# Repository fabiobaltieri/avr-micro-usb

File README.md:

AVR MICRO USB
==========

This project is a small USB key based on Atmel ATtiny45-like microcontrollers.

License
-------

This program is free software: you can redistribute it and/or modify
it under the terms of the GNU General Public License as published by
the Free Software Foundation, either version 2 of the License, or
(at your option) any later version.

Contents
--------

    COPYING     text version of the GPL
    README      this file
    firmware/   source directory for firmware files
    hardware/   source directory for the hardware design files

Firmware
--------

Building requires an avr-gcc toolchain, in the firmware/ directory, to build
run:

    make main.hex

Flashing the firmware on the device requires avrdude and a compatible hardware
programmer. Default configuration is stored at the beginning of the Makefile.
To program with the default configuration, run:

    make flash

Fuses can be configured running:

    make fuses

Hardware
--------

All hardware files (schematic, layout and libraries) are in CadSoft Eagle
format.

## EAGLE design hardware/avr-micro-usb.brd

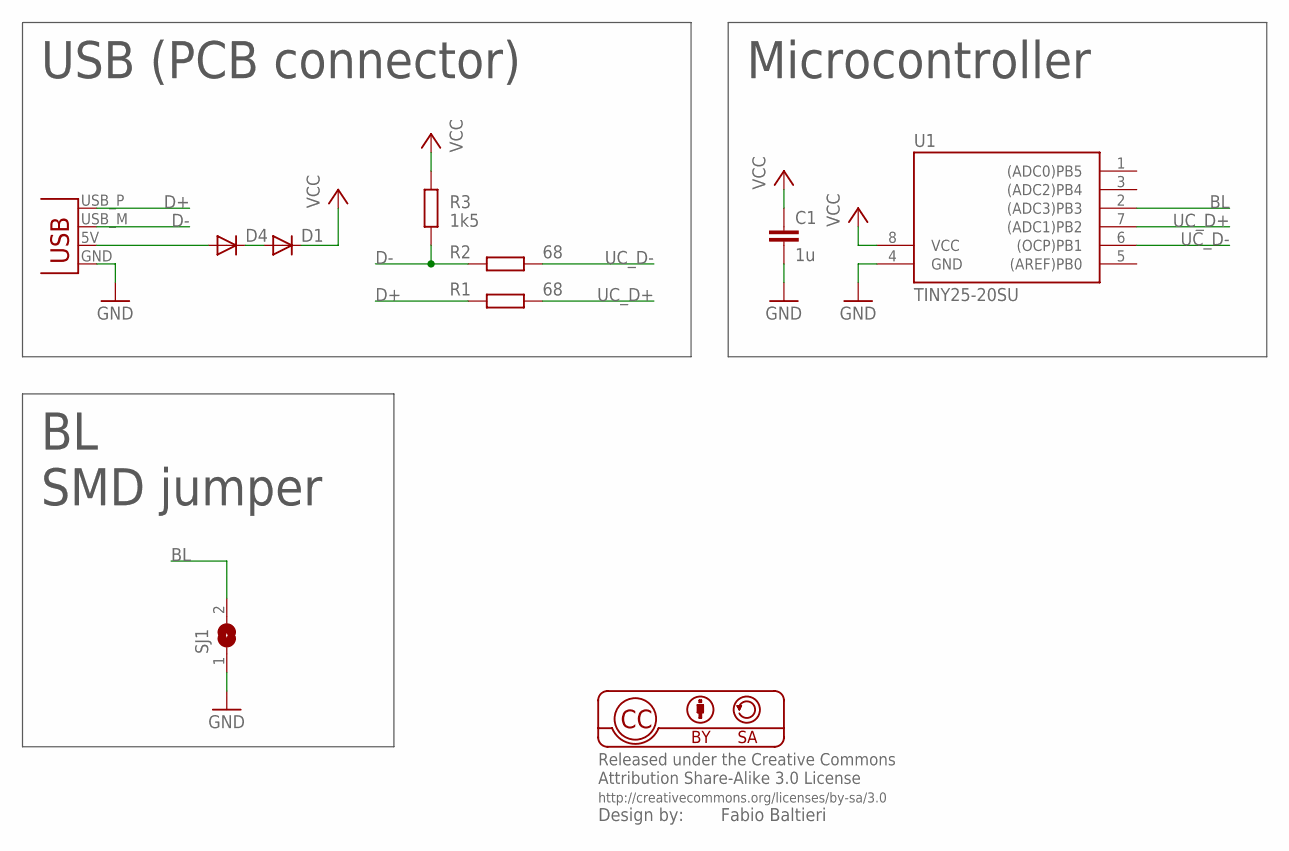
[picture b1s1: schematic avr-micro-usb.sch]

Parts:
C1: 1u; C0805
D1, D4: DIODE-MINIMELF; MINIMELF
R1, R2: 68; R0603
R3: 1k5; R0603
SJ1: SJ
U1: TINY25-20SU; SOIC8
X1: USBPCB; USB-A-PCB

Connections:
BL: SJ1.2, U1.2 ((ADC3)PB3)
D+: R1.2, X1.USB_P (D+)
D-: R2.2, R3.1, X1.USB_M (D-)
GND: C1.2, SJ1.1, U1.4 (GND), X1.GND
unnamed: D4.A, X1.5V (VBUS)
unnamed: D1.A, D4.C
UC_D+: R1.1, U1.7 ((ADC1)PB2)
UC_D-: R2.1, U1.6 ((OCP)PB1)
VCC: C1.1, D1.C, R3.2, U1.8 (VCC)

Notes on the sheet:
USB (PCB connector)
SMD jumper
Microcontroller

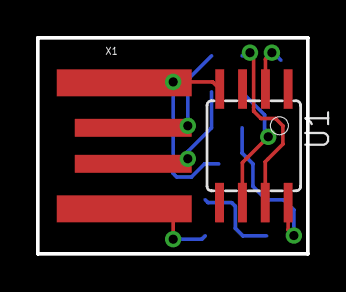
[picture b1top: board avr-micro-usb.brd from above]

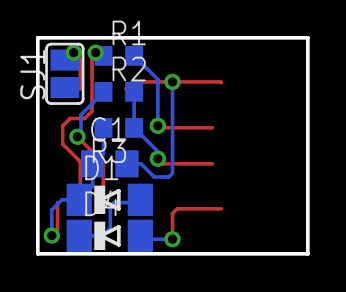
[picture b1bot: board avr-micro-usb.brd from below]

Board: 2 copper layers, 15.0 x 12.0 mm, 9 parts (7 on the bottom side), 9 nets.

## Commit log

2011-09-22 add README and license file
2011-09-22 firmware: add firwmare directory
    The initial firmware is based upon the one provided with the v-usb
    examples.
2011-09-22 hardware: add hardware directory
2011-09-22 hardware: add schematics in pdf version
2011-09-25 firmware-sensor: add firmware for key in sensor mode
2011-09-25 usbconfig.h: changed vendor and product string
2011-10-19 firmware-keyboard: add original keyboard firmware
2011-10-19 firmware-keyboard: remove old usbdrv lib
2011-10-19 firmware-keyboard: add new usbdrv lib
2011-10-19 Makefile: set MCU to attiny25
2011-10-19 usbconfig.h: change config to attinyx5
2011-10-19 usbconfig: remove vendor and product strings to save space
2011-10-19 main: initial attiny25 support
2011-10-19 main: change key report to MENU
2011-10-19 main: remove wrong port configurations for attiny25
2011-11-20 Update copyright information
2011-11-20 LICENSE: update to gplv3
2011-11-20 hardware: add CC BY-SA license
2012-01-24 hardware: convert files to v6, cosmetic changes
2012-03-20 firmware-nikon-remote: add clean firmware for nikon-remote
2012-03-20 firmware-nikon-remote: implement all requests
2012-03-31 nikon-ir: add shoot script
2012-04-01 nikon-trigger: change device name to IR-Trigger
2012-05-05 kernel-led: add avr-usb-led driver
2012-05-20 fw-nikon-remote: shot with irq disabled
2012-05-20 fw-nikon-remote: add copyright notes
